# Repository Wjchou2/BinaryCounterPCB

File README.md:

<br>
A Simple Binary counter using NE555 and CD4040 ICs and powered by a USB A receptacle. The Board includes 2 buttons (Increment and Reset) and an array of 4x3 LEDs that can show represent a count up to 4095.
To read the binary number, simply add up all the values of the lit up LEDs, and thats the counter number!

[View KiCad board in KiCanvas](https://kicanvas.org/?repo=https%3A%2F%2Fgithub.com%2FWjchou2%2FBinaryCounterPCB%2Ftree%2Fmain%2Fsrc%2Fkicad)

## Schematic!

## PCB!

## 3d Render!

# Usage
- Soldier all the parts onto the board
- Connect to a power source via the USB A receptacle
- Use the buttons to increment and reset the counter!

# BOM

|Id |Designator                              |Footprint                                       |Quantity|Designation|
|---|----------------------------------------|------------------------------------------------|--------|-----------|
|1  |D11,D9,D1,D5,D8,D7,D2,D3,D6,D4,D10,D12  |LED_D5.0mm                                      |12      |LED        |
|2  |C1                                      |C_Disc_D8.0mm_W5.0mm_P5.00mm                    |1       |10 uF      |
|3  |R1                                      |R_Axial_DIN0204_L3.6mm_D1.6mm_P7.62mm_Horizontal|1       |100k       |
|4  |J1                                      |USB_A_Molex_67643_Horizontal                    |1       |USB_A      |
|5  |R7,R9,R5,R10,R13,R6,R11,R12,R4,R3,R8,R14|R_Axial_DIN0204_L3.6mm_D1.6mm_P7.62mm_Horizontal|12      |450Ω       |
|6  |U1                                      |DIP-8_W7.62mm                                   |1       |NE555D     |
|7  |C2                                      |C_Disc_D8.0mm_W5.0mm_P5.00mm                    |1       |0.01 µF    |
|8  |R2,R15                                  |R_Axial_DIN0204_L3.6mm_D1.6mm_P7.62mm_Horizontal|2       |10k        |
|9  |SW2,SW1                                 |SW_PUSH-12mm                                    |2       |SW_Push    |
|10 |C3                                      |C_Disc_D8.0mm_W5.0mm_P5.00mm                    |1       |0.1 uF     |
|11 |U2                                      |DIP-16_W7.62mm                                  |1       |4040       |

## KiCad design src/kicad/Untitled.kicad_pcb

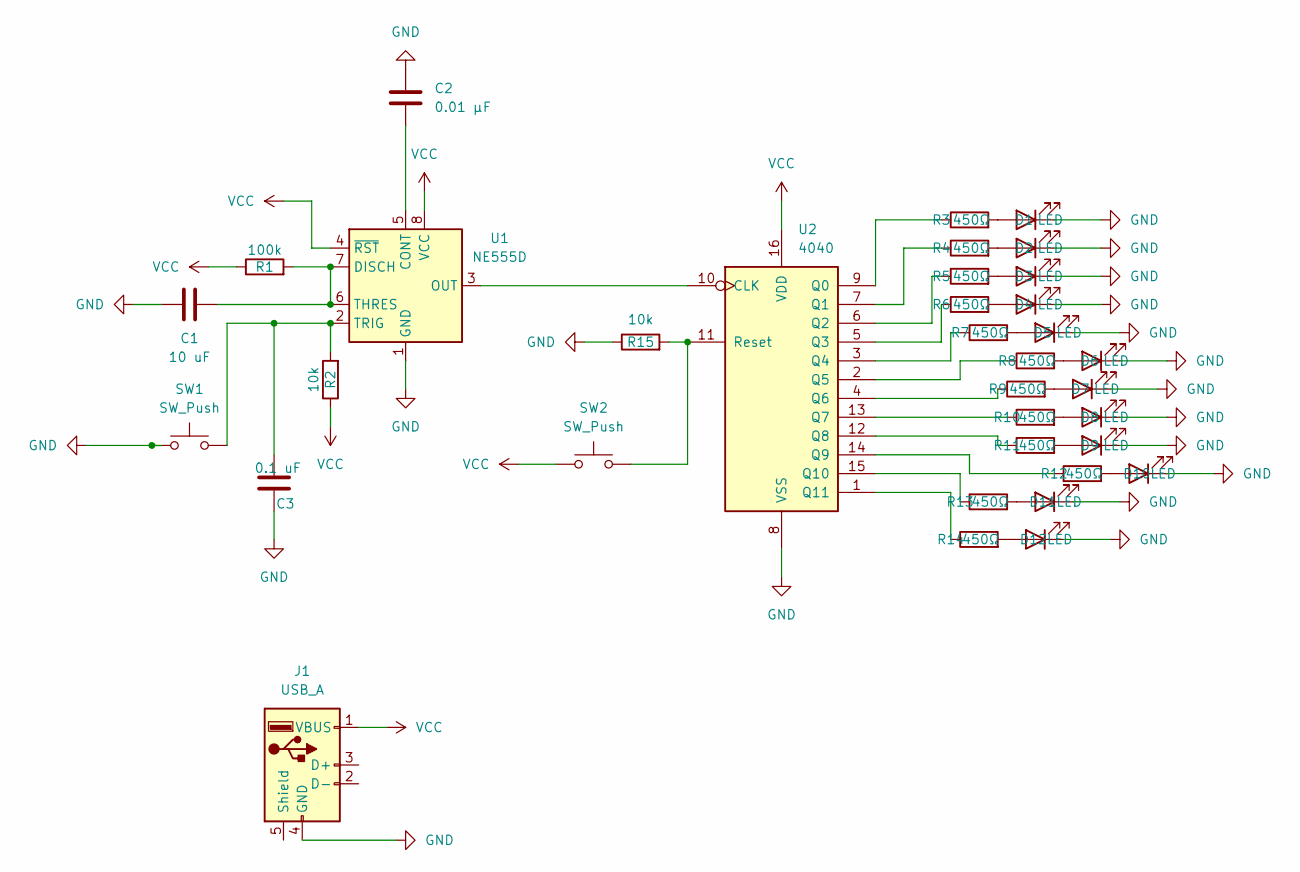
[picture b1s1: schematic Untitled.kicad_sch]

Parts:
C1: 10 uF; C_Disc_D8.0mm_W5.0mm_P5.00mm
C2: 0.01 µF; C_Disc_D8.0mm_W5.0mm_P5.00mm
C3: 0.1 uF; C_Disc_D8.0mm_W5.0mm_P5.00mm
D1, D2, D3, D4, D5, D6, D7, D8, D9, D10, D11, D12: LED; LED_D5.0mm
J1: USB_A; USB_A_Molex_67643_Horizontal
R1: 100k; R_Axial_DIN0204_L3.6mm_D1.6mm_P7.62mm_Horizontal
R2, R15: 10k; R_Axial_DIN0204_L3.6mm_D1.6mm_P7.62mm_Horizontal
R3, R4, R5, R6, R7, R8, R9, R10, R11, R12, R13, R14: 450Ω; R_Axial_DIN0204_L3.6mm_D1.6mm_P7.62mm_Horizontal
SW1, SW2: SW_Push; SW_PUSH-12mm
U1: NE555D; DIP-8_W7.62mm
U2: 4040; DIP-16_W7.62mm

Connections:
GND: C1.2, C2.1, C3.2, D1.1 (K), D2.1 (K), D3.1 (K), D4.1 (K), D5.1 (K), D6.1 (K), D7.1 (K), D8.1 (K), D9.1 (K), D10.1 (K), D11.1 (K), D12.1 (K), J1.4 (GND), R15.1, SW1.1, U1.1 (GND), U2.8 (VSS)
unnamed: D1.2 (A), R3.2
unnamed: D2.2 (A), R4.2
unnamed: D3.2 (A), R5.2
unnamed: D4.2 (A), R6.2
unnamed: D5.2 (A), R7.2
unnamed: D6.2 (A), R8.2
unnamed: D7.2 (A), R9.2
unnamed: D8.2 (A), R10.2
unnamed: D9.2 (A), R11.2
unnamed: D10.2 (A), R12.2
unnamed: D11.2 (A), R13.2
unnamed: D12.2 (A), R14.2
unnamed: C2.2, U1.5 (CONT)
unnamed: C1.1, R1.2, U1.6 (THRES), U1.7 (DISCH)
unnamed: U1.3 (OUT), U2.10 (CLK)
unnamed: C3.1, R2.2, SW1.2, U1.2 (TRIG)
unnamed: R3.1, U2.9 (Q0)
unnamed: R4.1, U2.7 (Q1)
unnamed: R5.1, U2.6 (Q2)
unnamed: R6.1, U2.5 (Q3)
unnamed: R7.1, U2.3 (Q4)
unnamed: R8.1, U2.2 (Q5)
unnamed: R9.1, U2.4 (Q6)
unnamed: R10.1, U2.13 (Q7)
unnamed: R11.1, U2.12 (Q8)
unnamed: R12.1, U2.14 (Q9)
unnamed: R13.1, U2.15 (Q10)
unnamed: R14.1, U2.1 (Q11)
unnamed: R15.2, SW2.2, U2.11 (Reset)
VCC: J1.1 (VBUS), R1.1, R2.1, SW2.1, U1.4 (~RST), U1.8 (VCC), U2.16 (VDD)

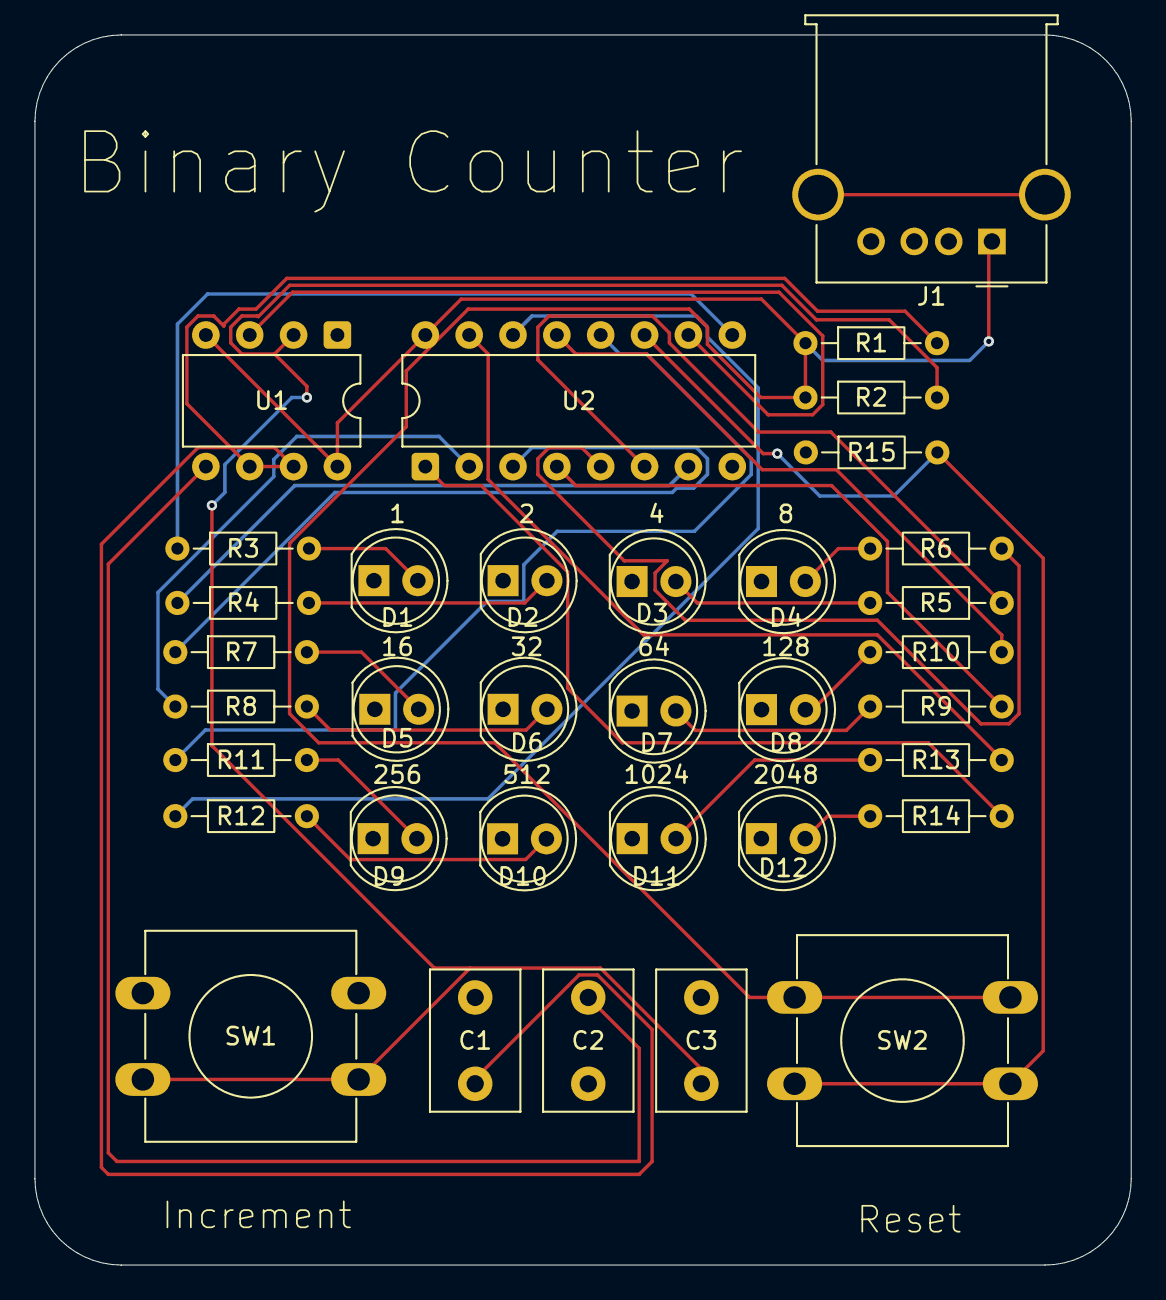
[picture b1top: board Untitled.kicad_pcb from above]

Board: 2 copper layers, 63.5 x 71.2 mm, 35 parts (0 on the bottom side), 31 nets.

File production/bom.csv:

Designator,Footprint,Quantity,Value,LCSC Part #
C1,C_Disc_D8.0mm_W5.0mm_P5.00mm,1,10 uF,
C2,C_Disc_D8.0mm_W5.0mm_P5.00mm,1,0.01 µF,
C3,C_Disc_D8.0mm_W5.0mm_P5.00mm,1,0.1 uF,
"D1, D10, D11, D12, D2, D3, D4, D5, D6, D7, D8, D9",LED_D5.0mm,12,LED,
J1,USB_A_Molex_67643_Horizontal,1,USB_A,
R1,R_Axial_DIN0204_L3.6mm_D1.6mm_P7.62mm_Horizontal,1,100k,
"R10, R11, R12, R13, R14, R3, R4, R5, R6, R7, R8, R9",R_Axial_DIN0204_L3.6mm_D1.6mm_P7.62mm_Horizontal,12,450Ω,
"R15, R2",R_Axial_DIN0204_L3.6mm_D1.6mm_P7.62mm_Horizontal,2,10k,
"SW1, SW2",SW_PUSH-12mm,2,SW_Push,
U1,DIP-8_W7.62mm,1,NE555D,
U2,DIP-16_W7.62mm,1,4040,

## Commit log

2026-04-17 vault backup: 2026-04-17 10:15:08
2026-04-17 vault backup: 2026-04-17 10:32:08
2026-04-17 vault backup: 2026-04-17 10:32:20
2026-04-17 vault backup: 2026-04-17 10:40:28
2026-04-17 vault backup: 2026-04-17 10:41:07
2026-04-17 vault backup: 2026-04-17 10:41:28
